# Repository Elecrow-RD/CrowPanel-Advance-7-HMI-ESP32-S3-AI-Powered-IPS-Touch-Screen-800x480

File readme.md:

## Menu
### 1, Product picture
### 2, Product version number
### 3, product information
### 4, Use the driver module
### 5,Quick Start
### 6,Folder structure.
### 7,Pin definition
### 8,Guidelines for downloading some of the files from the github repository

### 1, Product picture

#### 2, Product version number

|      | Hardware | Software | Remark |
| ---- | -------- | -------- | ------ |
| 1    | V1.0     | V1.0     | old    |
| 2    | V1.2     | V1.2     | old |
| 3    | V1.3     | V1.3     | old |
| 4    | V1.4     | V1.3     | old |
| 4    | V1.5     | V1.3     | latest |

### Version update points:

**Version 1.2**

① Version 1.2 updated the control of backlight on the basis of the original, the backlight of version 1.2 is controlled by STC8H1K28 microcontroller, and the backlight is lit in the program by sending the value to this microcontroller address (0x30).
The values are 0x05, 0x06, 0x07, 0x08, 0x09 and 0x10, where 0x05 switches off the backlight and 0x10 is the maximum brightness.

**To set a different brightness level, you must first send 0x10 to turn on the screen, and then send another value to adjust the brightness.**

The control of the buzzer is similar to that of the backlight: sending 0x15 activates the buzzer, while sending 0x16 deactivates it.

The speaker is controlled in the same manner: sending 0x17 activates the speaker, while sending 0x18 deactivates it.

② Version 1.2 has a new option for function switching, see above for details.
When using the case, please select the corresponding program to test or modify according to the version number of your motherboard.

**Version 1.3**

① Version 1.3 introduces an updated backlight control function. In this iteration, the backlight is managed by the STC8H1K28 microcontroller. The programme illuminates the backlight by transmitting numerical values to the microcontroller's address (0x30).
Brightness adjustment spans 0-245 levels, where 0 denotes maximum brightness, 244 represents minimum brightness, and 245 disables the backlight.

The buzzer control principle mirrors that of the backlight: sending 246 activates the buzzer, while sending 247 deactivates it.

**Version 1.4**

Only the button component has been updated. All other hardware and I/O pins remain the same as in the 1.3 version.

**Version 1.5**

Version 1.5 is simply an update to the previous version that modifies the packaging of the touchscreen FPC connector. There are no other differences.

### 3, product information

| Main Chip-ESP32-S3-WROOM-1-N16R8         |                                                              |
| -------------------------------------------- | ------------------------------------------------------------ |
| CPU/SoC                                      | high-performance Xtensa 32-bit LX7 dual-core processor, with up to 240MHz |
| System Memory                                | 512KB SRAM、8M PSRAM                                         |
| Memory                                       | 16M Flash，384KB ROM                                         |
| Development Language                         | MicroPython、C/C++                                           |
| Development Environment                      | ESP-IDF、Arduino IDE、PlatformIO、MicroPython         |
| **Screen**                                   |                                                              |
| Size                                         | 7.0 inch                                                     |
| Diver IC                                     | SC7277                                                       |
| Resolution                                   | 800*480                                                      |
| Display Panel                                | IPS Panel                                                    |
| Touch Panel                                  | Capacitive Single Touch                                      |
| Viewing Angle                                | 178°                                                         |
| Brightness                                   | 400 cd/m²(Typ.)                                              |
| Color Depth                                  | 16-bit                                                       |
| **Wireless Communication - Onboard Antenna** |                                                              |
| WiFi                                         | Support 2.4GHz, 802.11a/b/g/n                                |
| Bluetooth                                    | Support Bluetooth 5.0 and BLE                                |
| Other                                        | **Zigbee、LoRa、nRF2401、Matter、Thread and Wi-Fi 6 (Optional)** |
| **Interface/Function**                       |                                                              |
| Interface                                    | USB port, UART, I2C, SD card slot, battery socket, speaker port, microphone, etc. |
| Function                                     | RTC clock, audio amplifier, volume control, battery charge management, USB to UART, etc. |
| **Button/LED Indicator**                     |                                                              |
| Reset Button                                 | Yes, press to reset the device                               |
| Boot Button                                  | Yes, press and hold the power button to burn the program     |
| PWR                                          | Power indicator                                              |
| CHG                                          | Lithium battery charging status, completion indication       |
| **Other**                                    |                                                              |
| Installation method                          | Back hanging, fixed hole                                     |
| Operating temperature                        | -20~70 °C                                                    |
| Storage temperature                          | -30~80 °C                                                    |
| Power Input                                  | 5V/2A, USB or UART terminal                                  |
| Active Area                                  | 156mm*87mm                                                   |
| Dimensions                                   | 181.26\*108.36*16mm                                           |

### 4, Use the driver module

| Name | dependency library                      |
| ---- | --------------------------------------- |
| LVGL | lvgl/lvgl@8.3.3                         |
|      | Adafruit GFX Library<br/>version=1.11.0 |

### 5,Quick Start
### Arduino IDE starts

#### Teaching Case Path：./example/example_code7.0

1.Download the library files used by this product to the 'libraries' folder.

C:\Users\Documents\Arduino\libraries\

2.Open the Arduino IDE

3.Open the code configuration environment and burn it

### ESP-IDF starts

#### Teaching Case Path：./example/idf_code

1.Right-click on an empty space in the project folder and select "Open with VS Code" to open the project.

2.In the IDF plug-in, select the port, then compile and flash

### 6,Folder structure.

|--3D file： Contains 3D model files (.stp) for the hardware. These files can be used for visualization, enclosure design, or integration into CAD software.

|--Datasheet: Includes datasheets for components used in the project, providing detailed specifications, electrical characteristics, and pin configurations.

|--Eagle_SCH&PCB: Contains **Eagle CAD** schematic (`.sch`) and PCB layout (`.brd`) files. These are used for circuit design and PCB manufacturing.

|--example: Provides example code and projects to demonstrate how to use the hardware and libraries. These examples help users get started quickly.

|--factory_firmware: Stores pre-compiled factory firmware that can be directly flashed onto the device. This ensures the device runs the default functionality.

|--factory_sourcecode:  Contains the source code for the factory firmware, allowing users to modify and rebuild the firmware as needed.

|--libraries: Includes necessary libraries required for compiling and running the project. These libraries provide drivers and additional functionalities for the hardware.

|--Squareline_studio Instructions for use: Squareline_studio instructions: Demonstrate the use of squareline studio.

### 7,Pin definition

#define HSPI_MISO  4

#define HSPI_MOSI  6

#define HSPI_SCLK  5

#define HSPI_SS    19

#define SD_MOSI 6

#define SD_MISO 4

#define SD_SCK  5

#define SD_CS   7 //The chip selector pin is not connected to IO

#define I2S_DOUT 12

#define I2S_BCLK 13

#define I2S_LRC 11

cfg.pin_sclk = 42;  // SPI、SCLK

cfg.pin_mosi = 39;  // SPI、CLK

cfg.pin_miso = -1;  // SPI、MISO

cfg.pin_dc = 41; 

#define TOUCH_GT911_SCL 16

#define TOUCH_GT911_SDA 15

### 8,Guidelines for downloading some of the files from the github repository

##### 1, open the link in your browser: https://downgit.github.io/

##### 2, paste the URL of the GitHub destination folder in the input box (example format: `https://github.com/username/repository name/tree/branch name/folder path`)

##### 3, even a that way to download the file.

①Click the “Create Download Link” button to create a download link, copy the link and open it with your browser to download the contents of the corresponding folder directly.

②Click Download, and you can also download it directly.

#### Note: DownGit downloads are stored by default in **your browser's default downloads folder**, usually:

- **Windows**: `C:\Users\your username\Downloads\` (downloads folder)
- **macOS**: `~/Downloads/` (downloads folder)
- **Linux**: `~/Downloads/` (Downloads folder)

If you change the default download path in your browser, the file will be stored in the download location you set. You can find the downloaded file path in your browser's **Download History** (shortcut `Ctrl + J` or `Cmd + J`).

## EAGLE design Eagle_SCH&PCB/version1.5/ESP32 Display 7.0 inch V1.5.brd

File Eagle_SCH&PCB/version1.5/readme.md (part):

# 7.0-Inch Hardware Identity Product Hardware Driver Guide

| Item | Details |
|---|---|
| Document Version | V1.0 |
| Corresponding Hardware Documentation | `ESP32 Display 7.0 inch V1.5.sch/.brd`, `ESP32-Display-7.0-inch-V1.5.pdf` |
| Preparation Date | 2026-07-30 |
| Author | OpenAI Codex (cross-compiled from project materials) |
| Scope | The 7.0-inch CrowPanel Advance HMI hardware in this repository and the accompanying Arduino validation projects |

> **Priority of conclusions:** Board-level driver code that has been successfully tested or delivered with the project > EAGLE `.sch` net connections > PDF visual annotations > general-purpose chip datasheets. This document uses the pins and parameters actually used by the code as the porting baseline. Functions confirmed only by the schematic and lacking validation programs in the repository are explicitly marked “To Be Verified” and must not be treated as production software acceptance results.

## 1. Document Sources and Evidence Levels

### 1.1 Input Materials

1. `version1.5/ESP32 Display 7.0 inch V1.5.sch`: Primary source for components, net names, and electrical connections.
2. `version1.5/ESP32-Display-7.0-inch-V1.5.pdf`: Source for functional sections, DIP-switch instructions, and visual verification.
3. `Arduino/lesson-01` through `lesson-09`: Examples for serial communication, audio, LCD/LVGL, TF card, expansion ports, nRF24L01, SX1262/LoRaWAN, and UART/Zigbee.
4. `Arduino/SD_CrowPanel_ESP32_Advance_HMI_4_3_5_0_7_0`: An additional TF card display example, used only to identify differences in historical parameters.
5. Library versions included with the repository: Arduino-ESP32 3.3.8 (specified in the README), LovyanGFX 1.2.25, LVGL 9.1.0, ESP32-audioI2S 3.4.7, RF24 1.6.1, and RadioLib 7.7.1.

### 1.2 Evidence Levels

| Level | Meaning | Usage Rule |
|---|---|---|
| A: Code-verified | Complete initialization and application read/write operations exist in the project examples | May be used directly as the porting baseline, but regression testing in the target firmware is still required |
| B: Schematic-confirmed | Complete connections exist in the schematic, but the repository has no corresponding read/write example | Pin connections are reliable; protocol parameters require first-board validation |
| C: External-module example | The example targets a module connected to an expansion port and does not represent an onboard component | Applicable only when the corresponding peripheral is installed and the DIP switches are configured correctly |
| D: Inferred/To Be Confirmed | Conflicts exist in model, address, or production-batch information | Must be verified against the physical unit and chip datasheet before use |

## 2. Product Architecture and Peripheral Overview

The main controller is an ESP32-S3-WROOM-1 module. The MCU section title in the schematic PDF is labeled `ESP32-S3-N16R8`, indicating that the target configuration is likely 16 MB Flash + 8 MB PSRAM; however, the laser marking on the physical module and the Arduino build menu must take precedence. The board also includes an STC8H1K28 auxiliary control MCU, which handles backlight control, touch reset, buzzer control, amplifier/board-level power control, and other functions over a shared I²C bus.

| Category | Component/Interface | Primary Connections | Driver Method | Level |
|---|---|---|---|---|
| Main Controller | ESP32-S3-WROOM-1 (shown as N16R8) | All main-controller GPIOs; USB-UART | Arduino-ESP32 / ESP-IDF HAL | A/D |
| Board Control MCU | STC8H1K28-36I-LQFP32 | I²C GPIO15/16, address `0x30`; GPIO1 recovery path | I²C single-byte commands | A |
| Display | 7.0-inch 800×480 RGB IPS | GPIO3/7/9~14/17/18/21/38/45~48, 39~42 | 16-bit RGB parallel interface + DMA | A |
| Touch | GT911 capacitive touch | SDA15, SCL16; INT to GPIO1; RST controlled by board control MCU | I²C at 400 kHz, address `0x5D` | A |
| Backlight | MT9201 boost constant-current driver + board control MCU | LCD LEDA/LEDK; MCU controls EN/power | I²C commands 0~245 | A |
| TF Card | MicroSD card slot | GPIO4 MISO, 5 SCK, 6 MOSI; CS fixed in hardware | SPI/FS/SD, 40 MHz | A |
| Audio Output | NS4168 digital-input amplifier + speaker connector | GPIO4 SDATA, 5 BCLK, 6 LRCLK | I²S; board control command `248` enables output | A |
| Digital Microphone | LMD3526B261 PDM MIC | GPIO19 CLK, GPIO20 DATA, through CH486F | PDM/I²S RX | B |
| RTC | PCF8563-compatible component + 32.768 kHz + CR1220 | SDA15, SCL16 | I²C, typically address `0x51` | B/D |
| Buzzer | 5025 passive buzzer + NPN | Controlled by STC8H1K28 P2.7 | Auxiliary MCU PWM/GPIO | B |
| Wireless Expansion | J9/J12 expansion ports | SPI GPIO4/5/6; control GPIO19/20, plus GPIO2/8 | SPI + GPIO/IRQ | C |
| nRF24L01 | External 2.4 GHz module | MISO4/MOSI6/SCK5, CSN19, CE20 | RF24; 250 kbps, CH50 | C |
| SX1262 | External LoRa module | NSS8, DIO1 20, RST19, BUSY2, SPI4/5/6 | RadioLib / LoRaWAN | C |
| UART Expansion | J2/J14/multiplexed port | UART0; or GPIO19 RX, GPIO20 TX | UART 8N1, example uses 115200 | A/C |
| I²C Expansion | J13/J11 | SDA15, SCL16, 3.3 V/GND | I²C, shared onboard bus | A/C |
| GPIO Expansion | J11 | GPIO2, GPIO8, I²C, power | 3.3 V GPIO | B/C |
| USB/Programming | USB-C + CH340K + automatic programming circuit | ESP UART0, EN, GPIO0 | USB-UART / automatic reset and programming | A |
| Battery/Charging | TP4059 + battery connector | USB/5 V, VBAT, CHRG/DONE to board control MCU | Hardware charging, MCU status acquisition | B |
| Main Power | RY3420/HM3416H DC-DC, etc. | VIN → 3.3 V; separate boost supply for display backlight | Hardware power management | B |
| Wi-Fi/BLE | ESP32-S3 integrated radio | Module antenna | Arduino WiFi/BLE stack | A (Wi-Fi) |
| Indicators/Buttons | BOOT, RESET, power/charging LEDs | GPIO0, EN; board control MCU | Active-low buttons/hardware indicators | A/B |

## 3. ESP32-S3 GPIO Baseline Table

| GPIO | Actual Function in Code | Schematic Net/Connection | Multiplexing and Considerations |
|---:|---|---|---|
| 0 | CS parameter passed to the SD library by the TF example; BOOT | `IO0_BOOT`, active-low BOOT button | **Boot strapping pin**; MicroSD CS is not physically connected to GPIO0 and must not be assumed to be controllable as a chip-select signal |
| 1 | Touch/board-control fault recovery: low pulse for 120 ms, then configured as input | `IO1_TP_INT`, touch FPC INT | No touch interrupt is registered at runtime; must not be continuously driven in push-pull mode |
| 2 | SX1262 BUSY; GPIO expansion | J11 GPIO; schematic `IO2` | Used as an input with external LoRa; consider boot state and peripheral signal levels |
| 3 | LCD R3 (logical R3 in code, physical panel R6) | `IO3_R6` | Dedicated to LCD; do not reuse |
| 4 | SD MISO / I²S SDATA / external SPI MISO | Through CH486F analog switch | Mutually exclusive; selected by DIP switch |
| 5 | SD SCK / I²S BCLK / external SPI SCK | Through CH486F analog switch | Mutually exclusive; clock lines must not be connected to multiple channels simultaneously |
| 6 | SD MOSI / I²S LRCLK / external SPI MOSI | Through CH486F analog switch | Mutually exclusive |
| 7 | LCD R0 (panel R3) | `IO7_R3` | Dedicated to LCD |
| 8 | SX1262 NSS; GPIO expansion | J11 GPIO; schematic `IO8` | Used as chip select in the LoRa example |
| 9~14 | LCD G0~G5 (panel G2~G7) | RGB data | Dedicated to LCD |
| 15 | I²C SDA | RTC, GT911, STC, I²C port | External open-drain, pulled up to 3.3 V; shared bus |
| 16 | I²C SCL | RTC, GT911, STC, I²C port | External open-drain, pulled up to 3.3 V; shared bus |
| 17,18 | LCD R1,R2 | RGB data | Dedicated to LCD |
| 19 | Expansion IRQ/CSN/RST/UART RX or PDM CLK | Through CH486F to wireless port/microphone | Multiplexed as a pair with GPIO20; enable only after configuring the DIP switches |
| 20 | Expansion CE/DIO1/UART TX or PDM DATA | Through CH486F to wireless port/microphone | Multiplexed as a pair with GPIO19 |
| 21 | LCD B0 | RGB data | Dedicated to LCD |
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
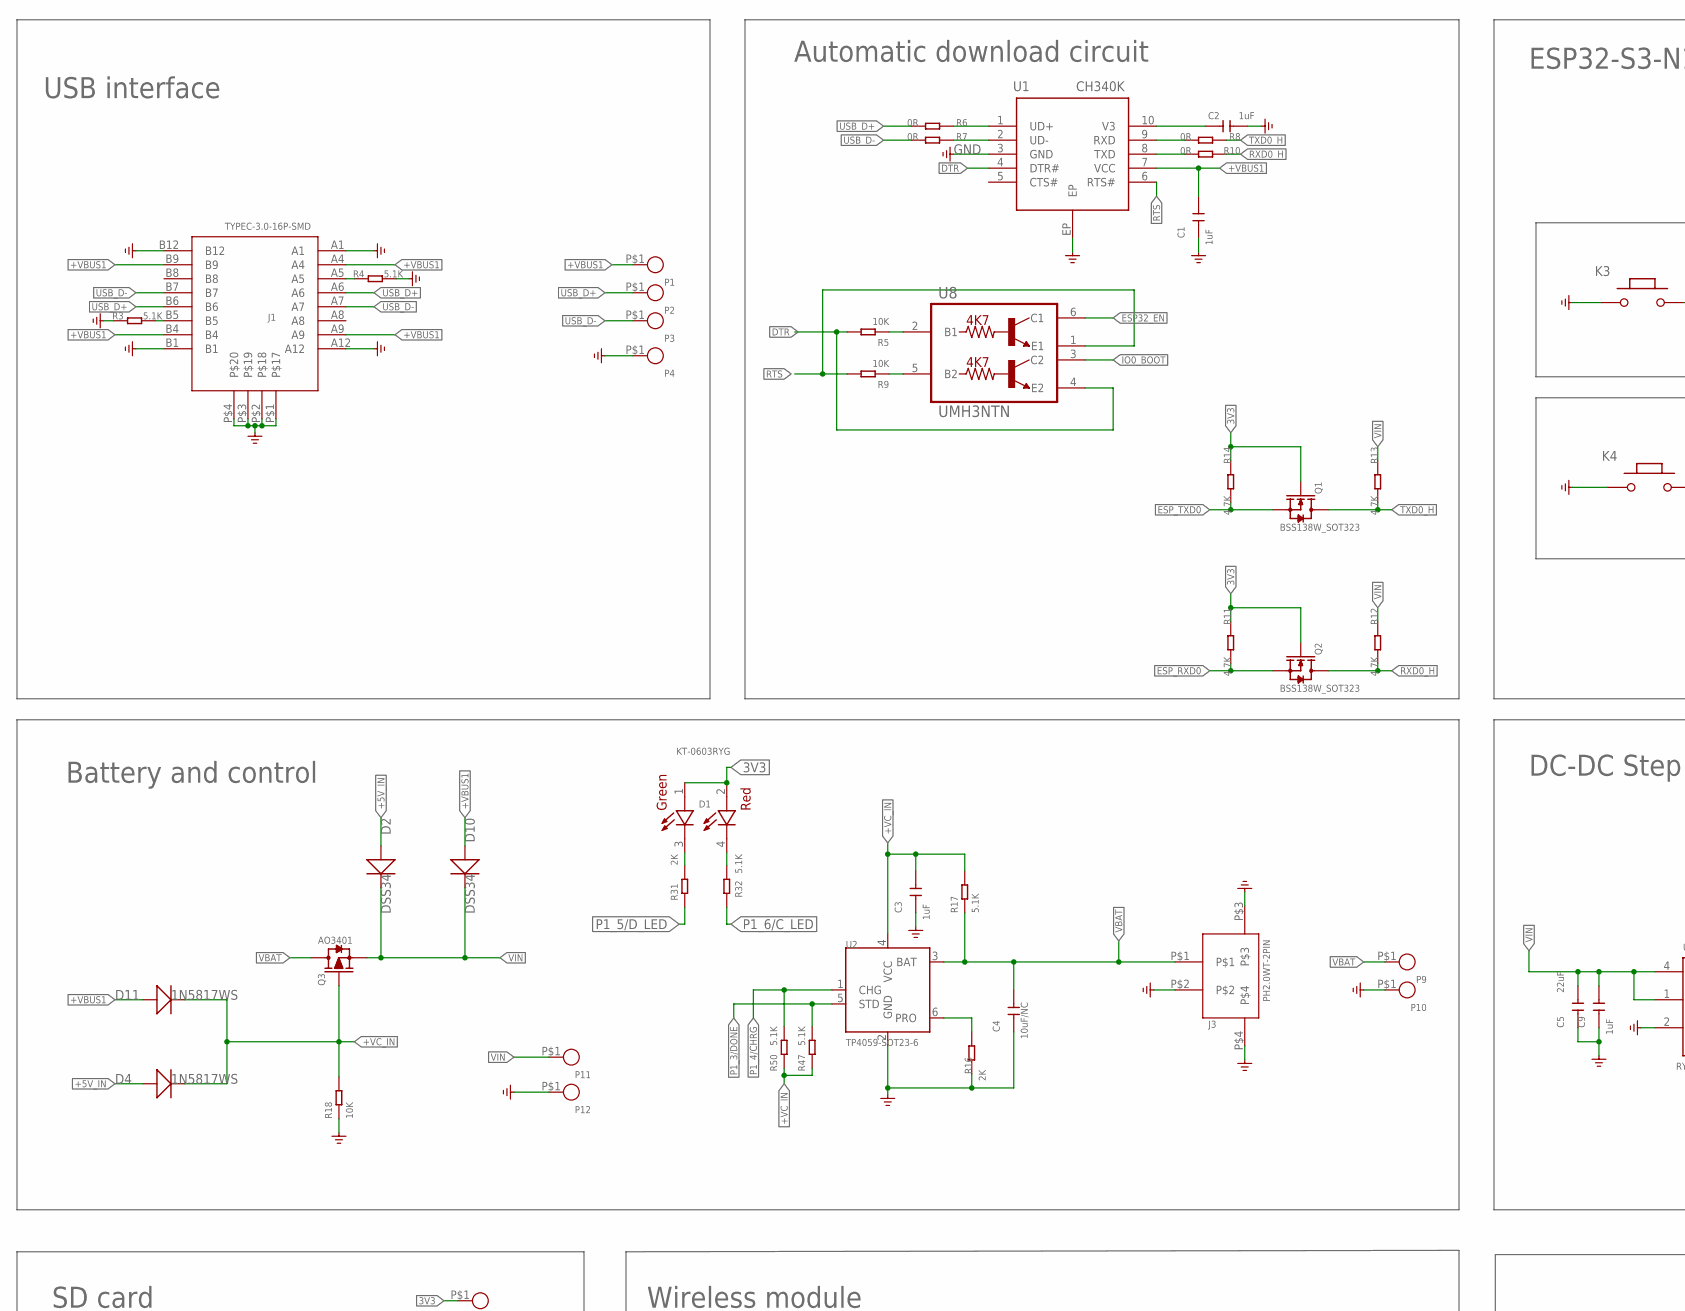
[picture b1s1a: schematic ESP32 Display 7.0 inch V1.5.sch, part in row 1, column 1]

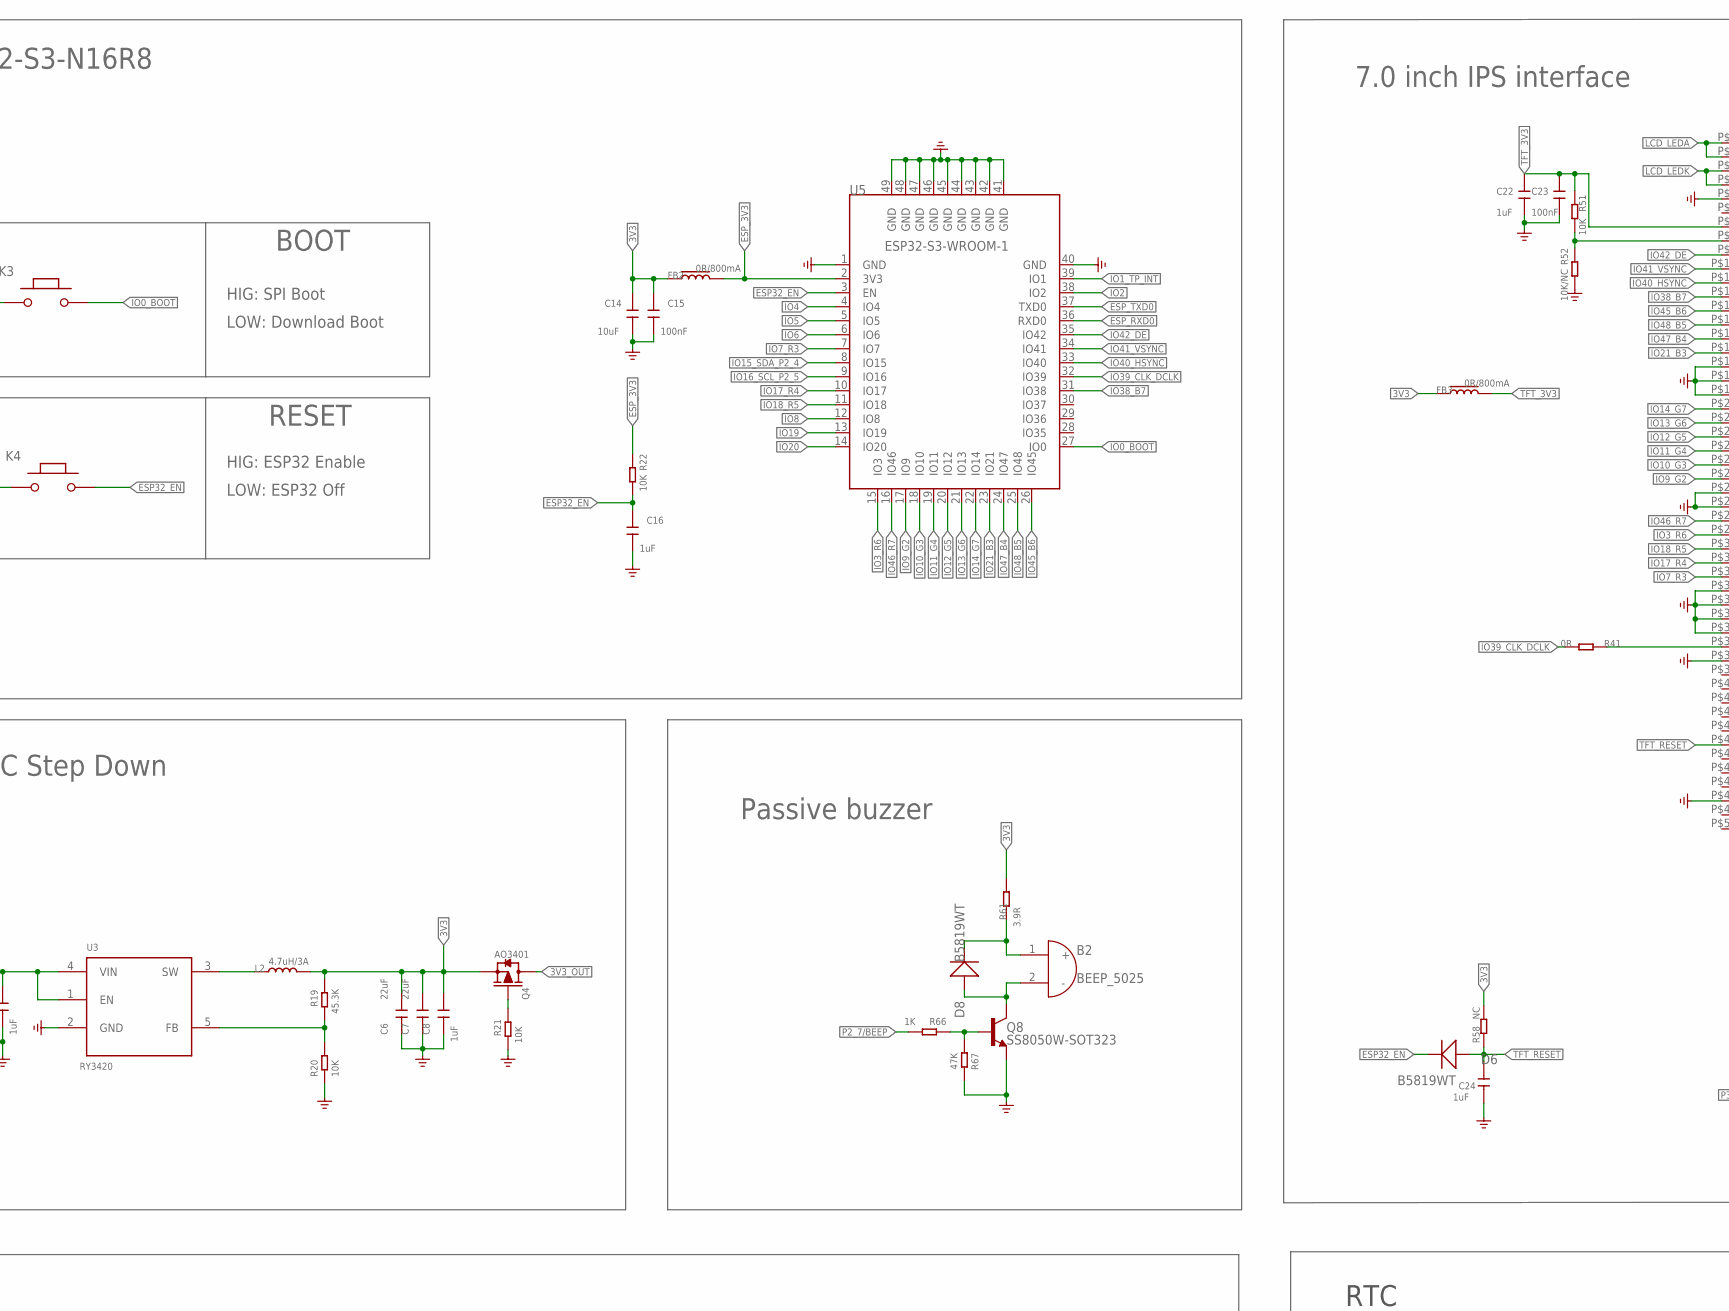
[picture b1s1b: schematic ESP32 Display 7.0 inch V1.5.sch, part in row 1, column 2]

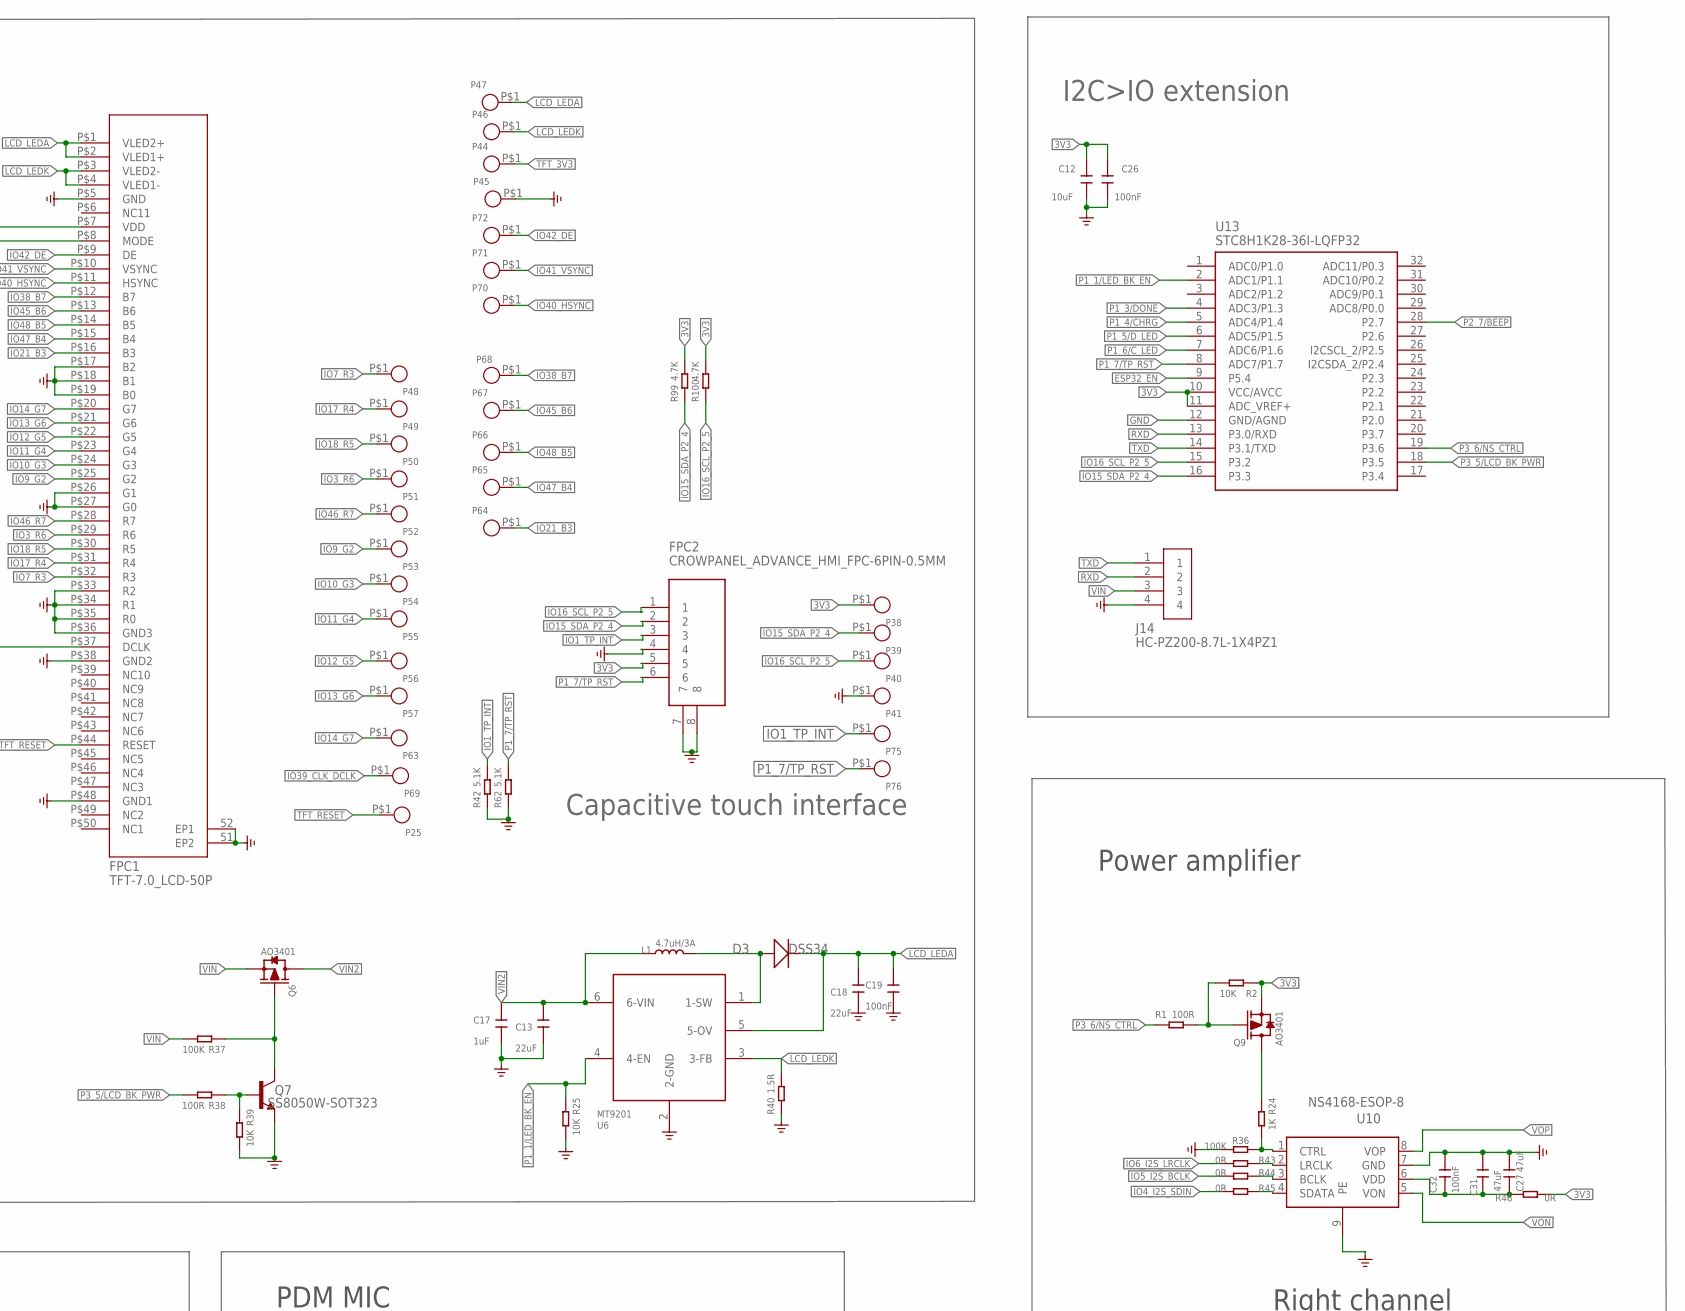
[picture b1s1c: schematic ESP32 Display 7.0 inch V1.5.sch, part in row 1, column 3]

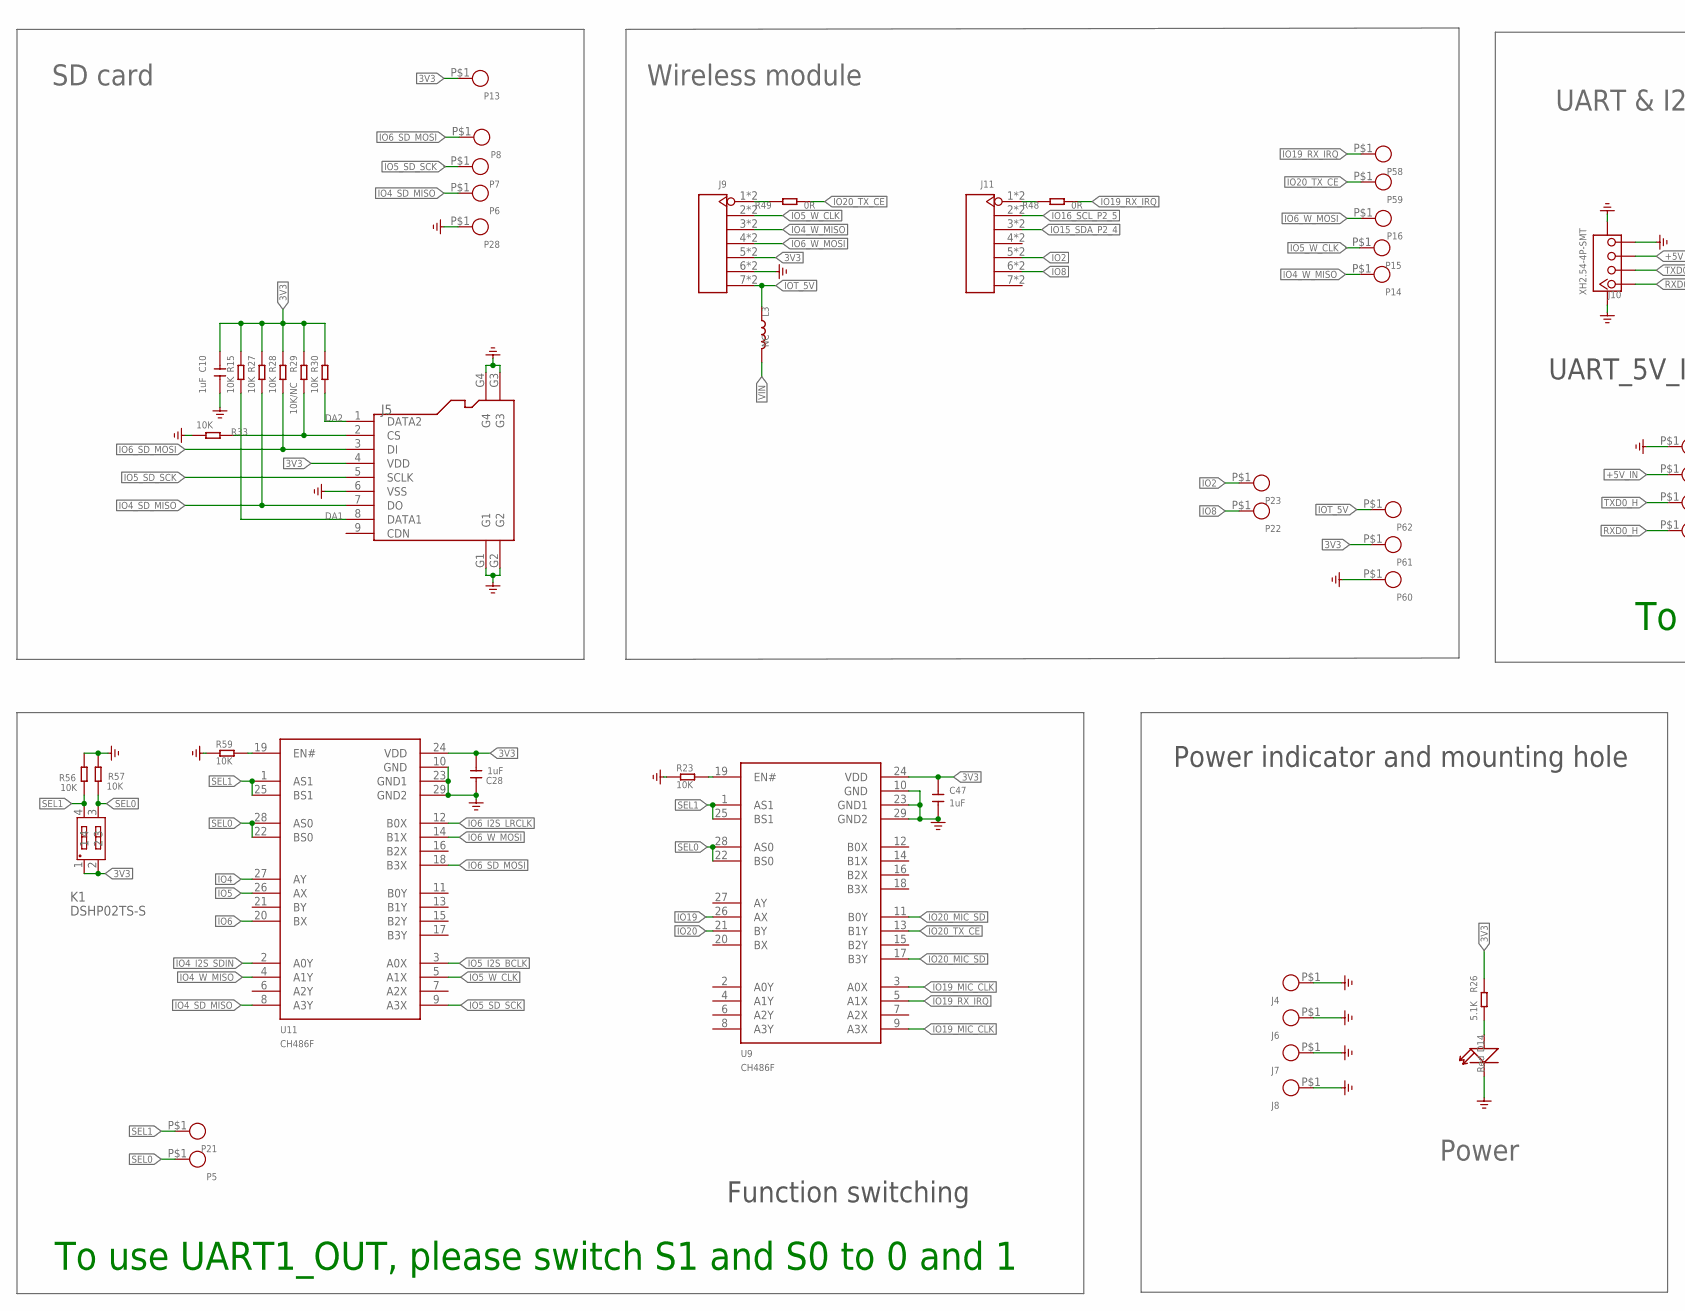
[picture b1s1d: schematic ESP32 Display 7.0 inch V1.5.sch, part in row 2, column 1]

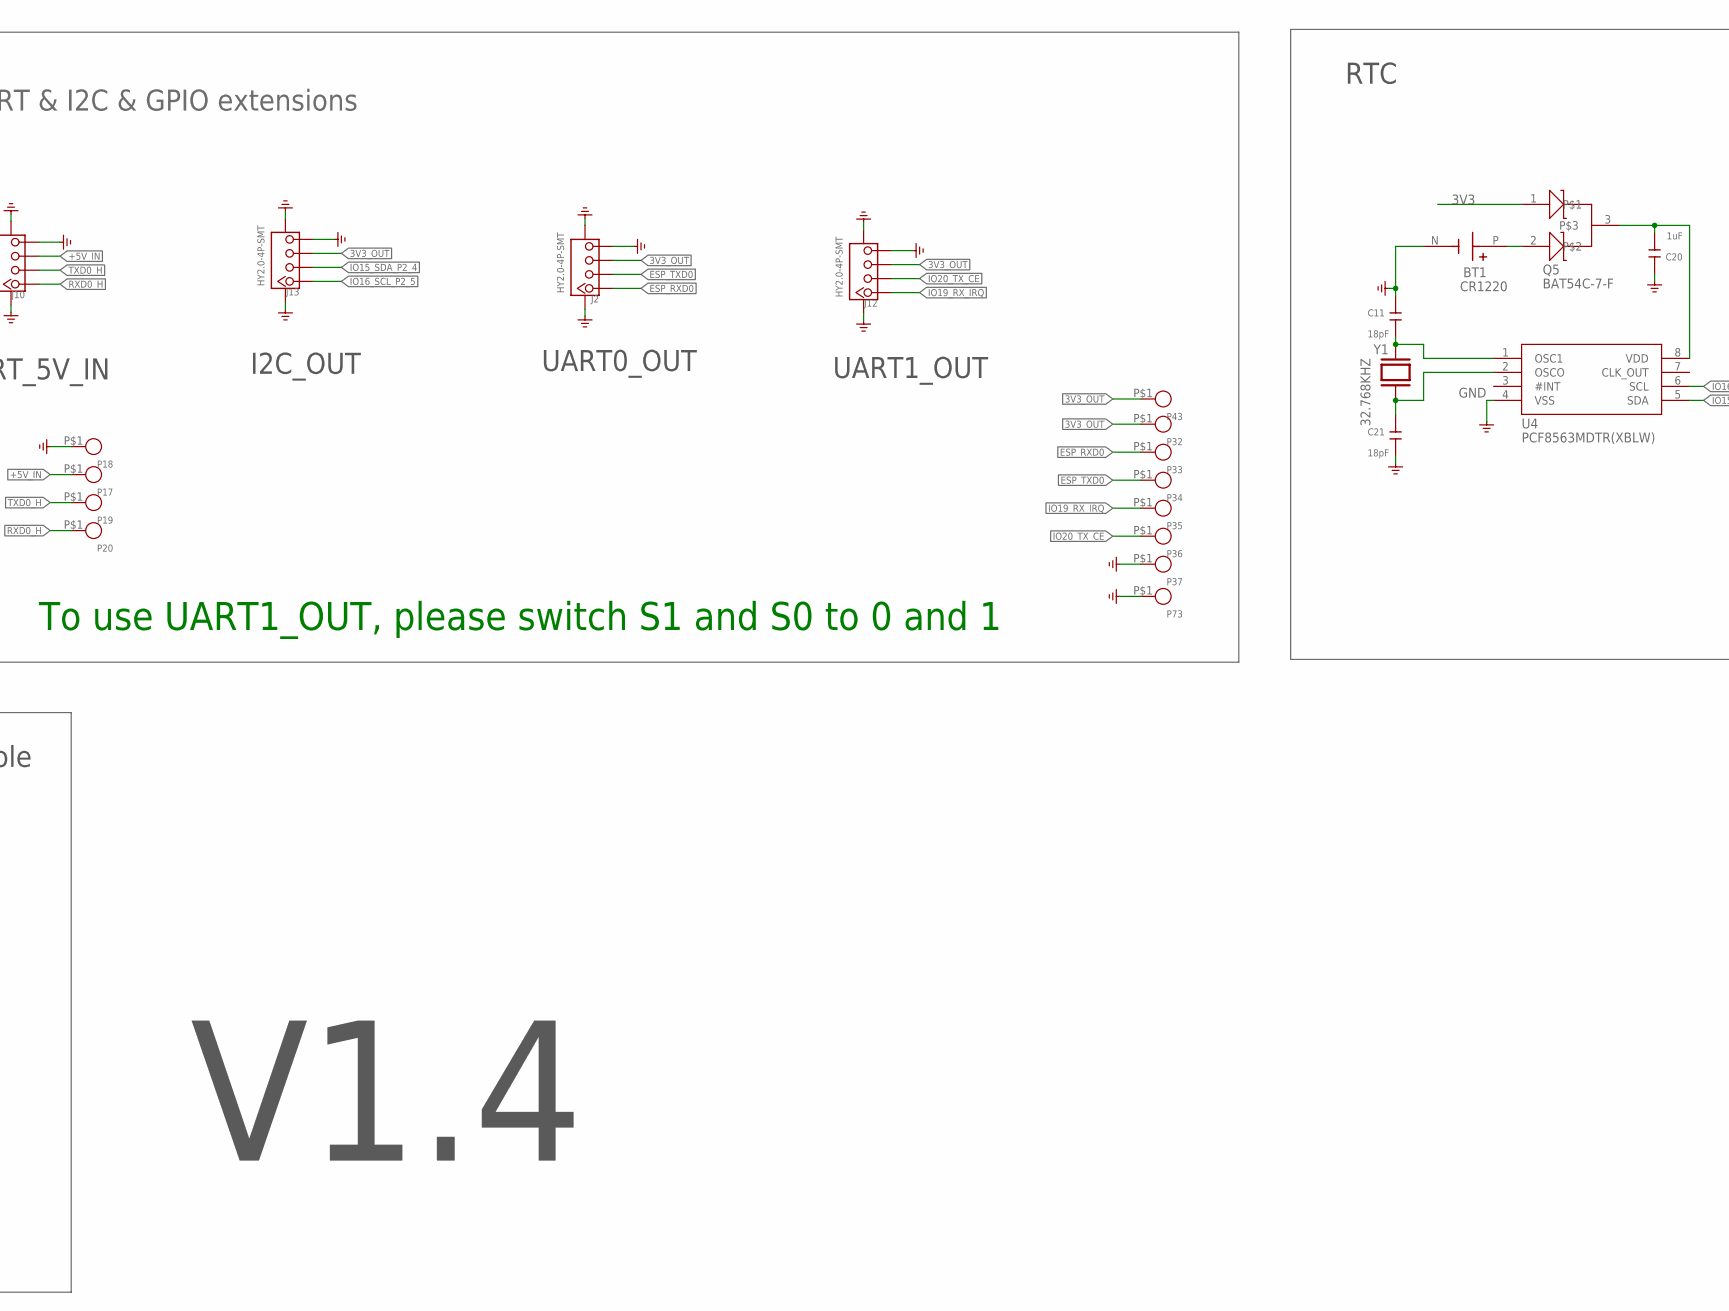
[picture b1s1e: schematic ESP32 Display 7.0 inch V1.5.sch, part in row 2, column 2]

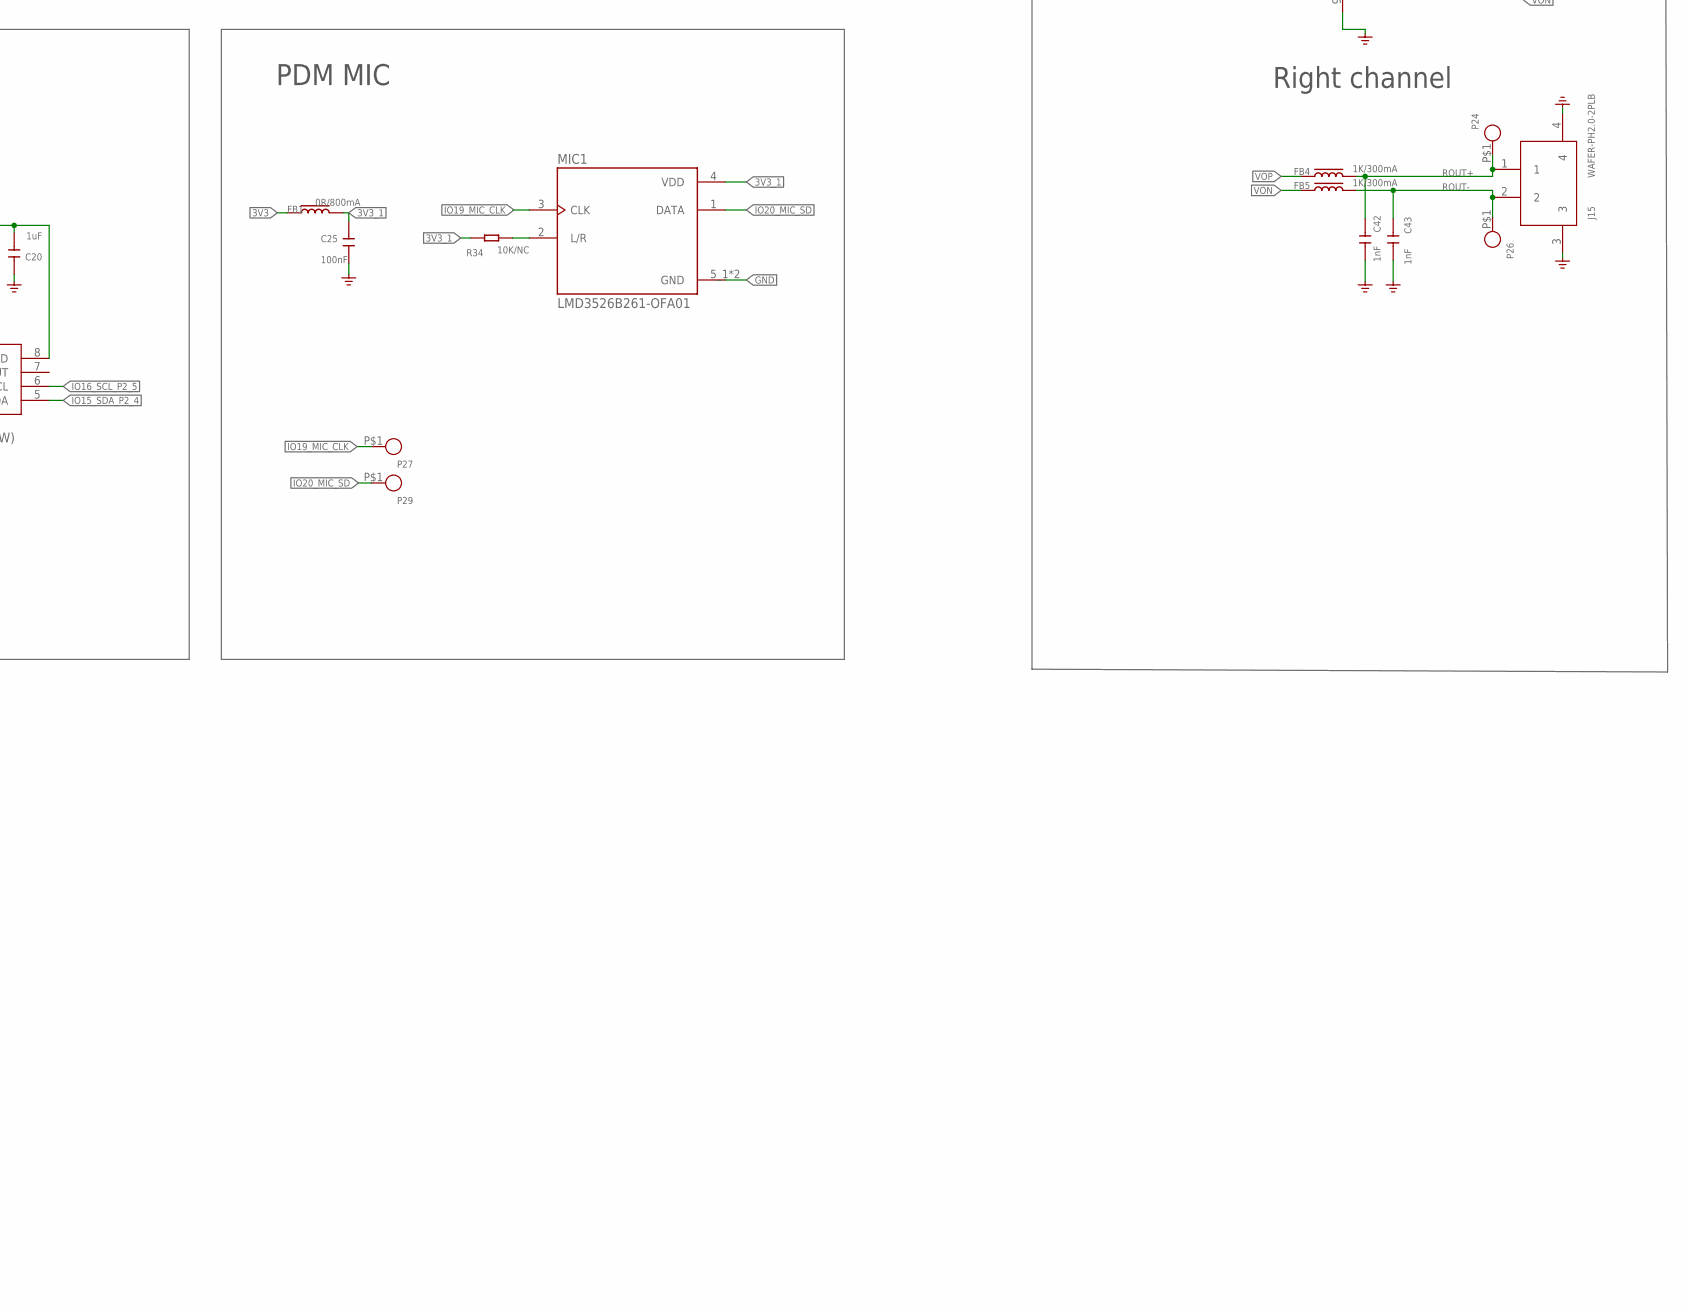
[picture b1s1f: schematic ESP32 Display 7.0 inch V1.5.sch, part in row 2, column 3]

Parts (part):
B2: BEEP_5025
BT1: CR1220
C1, C2, C3, C8, C9, C10, C16, C17, C20, C22, C24, C28, C47: 1uF; C0603
C4: 10uF/NC; C0603
C5, C6, C7, C13, C18: 22uF; C0805
C11, C21: 18pF; C0603
C12, C14: 10uF; C0603
C15, C19, C23, C25, C26, C32: 100nF; C0603
C27, C31: 47uF; C0805
C42, C43: 1nF; C0603
D1: KT-0603RYG; LED_KT-0603RYG
D2, D3, D10: DSS34; D_SOD123FL
D4, D11: 1N5817WS; D_SOD323
D6, D8: B5819WT; D_SOD523
D14: Red; LED0603
FB1, FB2, FB3: 0R/800mA; L0603
FB4, FB5: 1K/300mA; L0603
FPC1: TFT-7.0_LCD-50P; FPC-P0.5MM-50P-SMD
FPC2: CROWPANEL_ADVANCE_HMI_FPC-6PIN-0.5MM
J1: TYPEC-3.0-16P-SMD; USB-3.0TYPEC-SMD
J2, J12, J13: HY2.0-4P-SMT; CONNECTOR_4P-SMD-2.0
J3: PH2.0WT-2PIN
J4, J6, J7, J8: THO-M3.25MM-HOLE; THO-M3.2*5MM-HOLE
J5: HOLDER-MICROSD-9P; 9P-SMD-W/-RING
J9, J11: HEADER-7P-18.28X2.5; H7-2.54-18.28X2.5X5MM
J10: XH2.54-4P-SMT; XH2.54-4P-SMD
J14: HC-PZ200-8.7L-1X4PZ1; TEST-PIN-4-2.0MM
J15: WAFER-PH2.0-2PLB; CONN-TH_2P-P2.00_XUNPU_WAFER-PH2.0-2PLB
K1: DSHP02TS-S; SW-SMD_DSHP02TS-S_1
K3, K4: PB157; 157SW
L1, L2: 4.7uH/3A; L0420
L3: NC; L0603
MIC1: LMD3526B261-OFA01; MIC-SMD_5P-L3.5-W2.7-P1.67
P1, P2, P3, P4, P5, P6, P7, P8, P9, P10, P11, P12, P13, P14, P15, P16, P17, P18, P19, P20, P21, P22, P23, P24, P25, P26, P27, P28, P29, P32, P33, P34, P35, P36, P37, P38, P39, P40, P41, P43, P44, P45, P46, P47, P48, P49, P50, P51, P52, P53, P54, P55, P56, P57, P58, P59, P60, P61, P62, P63, P64, P65, P66, P67, P68, P69, P70, P71, P72, P73, P75, P76: TEST_PADPAD-1.5MM; TEST_PAD-1.5MM
Q1, Q2: BSS138W_SOT323; MOS_SOT323
Q3, Q4, Q6, Q9: AO3401; PMOS_SOT23
Q5: BAT54C-7-F; SOT-23
Q7, Q8: SS8050W-SOT323; MOS_SOT323
R1, R38: 100R; R0603-SP
R2, R5, R9, R15, R18, R20, R21, R22, R23, R25, R27, R28, R30, R33, R39, R51, R56, R57, R59: 10K; R0603-SP
R3, R4, R17, R26, R32, R42, R47, R50, R62: 5.1K; R0603-SP
R6, R7, R8, R10, R41, R43, R44, R45, R46, R48, R49: 0R; R0603-SP
R11, R12, R13, R14, R99, R100: 4.7K; R0603-SP
R16, R31: 2K; R0603-SP
R19: 45.3K; R0603-SP
R24, R66: 1K; R0603-SP
R29, R34, R52: 10K/NC; R0603-SP
R36, R37: 100K; R0603-SP
R40: 1.5R; R0603-SP
R58: NC; R0603-SP
R61: 3.9R; R0603-SP
R67: 47K; R0603-SP
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
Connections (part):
3V3: C6.2, C7.2, C8.2, C10.2, C12.2, C14.2, C15.2, C26.2, C28.2, C47.1, D1.1, D1.2, FB1.1, FB2.1, FB3.1, FPC2.5, J5.4 (VDD), J9.5, J9.5-5 (5), K1.1, K1.2, L2.2, P13.P$1, P38.P$1, P61.P$1, Q1.1 (G), Q2.1 (G), Q4.2 (S), Q5.1, Q9.2 (S), R2.1, R11.1, R14.1, R15.2, R19.2, R26.2, R27.2, R28.2, R29.2, R30.2, R46.2, R58.2, R61.2, R99.2, R100.2, U9.24 (VDD), U11.24 (VDD), U13.10 (VCC/AVCC), U13.11 (ADC_VREF+)
3V3$: C2.2, U1.10 (V3)
3V3_1: C25.2, FB1.2, MIC1.4 (VDD), R34.2
3V3_OUT: J2.3, J12.3, J13.3, P32.P$1, P43.P$1, Q4.3 (D)
+5V_IN: D2.+, D4.+, J10.3, P17.P$1
+VBUS1: C1.2, D10.+, D11.+, J1.A4, J1.A9, J1.B4, J1.B9, P1.P$1, U1.7 (VCC)
+VC_IN: C3.2, D4.-, D11.-, Q3.1 (G), R17.2, R18.2, R47.2, R50.2, U2.4 (VCC)
DA1: J5.8 (DATA1), R15.1
DA2: J5.1 (DATA2), R30.1
DTR: R5.2, U1.4 (DTR#), U8.4 (E2)
ESP32_EN: C16.2, D6.-, K4.2, R22.2, U5.3 (EN), U8.6 (C1), U13.9 (P5.4)
ESP_3V3: FB2.2, R22.1, U5.2 (3V3)
ESP_RXD0: J2.1, P33.P$1, Q2.2 (S), R11.2, U5.36 (RXD0)
ESP_TXD0: J2.2, P34.P$1, Q1.2 (S), R14.2, U5.37 (TXD0)
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
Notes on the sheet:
BOOT
RESET
HIG: SPI Boot
LOW: Download Boot
HIG: ESP32 Enable
LOW: ESP32 Off
Power
USB interface
Automatic download circuit
Battery and control
RTC
ESP32-S3-N16R8
7.0 inch IPS interface
Capacitive touch interface
DC-DC Step Down
SD card
Wireless module
UART & I2C & GPIO extensions
Power indicator and mounting hole
I2C>IO extension
PDM MIC
Power amplifier
Right channel
Passive buzzer
Function switching
UART_5V_IN
I2C_OUT
UART0_OUT
UART1_OUT
To use UART1_OUT, please switch S1 and S0 to 0 and 1
V1.4

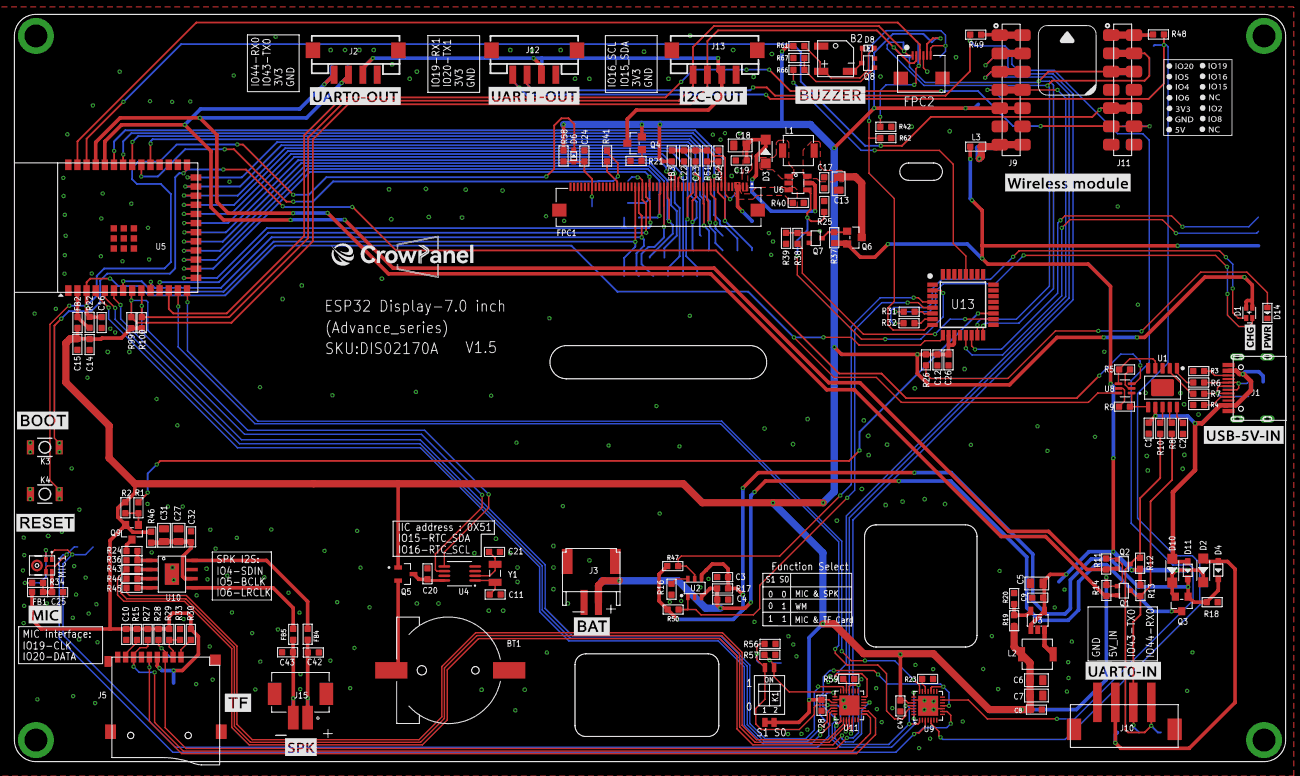
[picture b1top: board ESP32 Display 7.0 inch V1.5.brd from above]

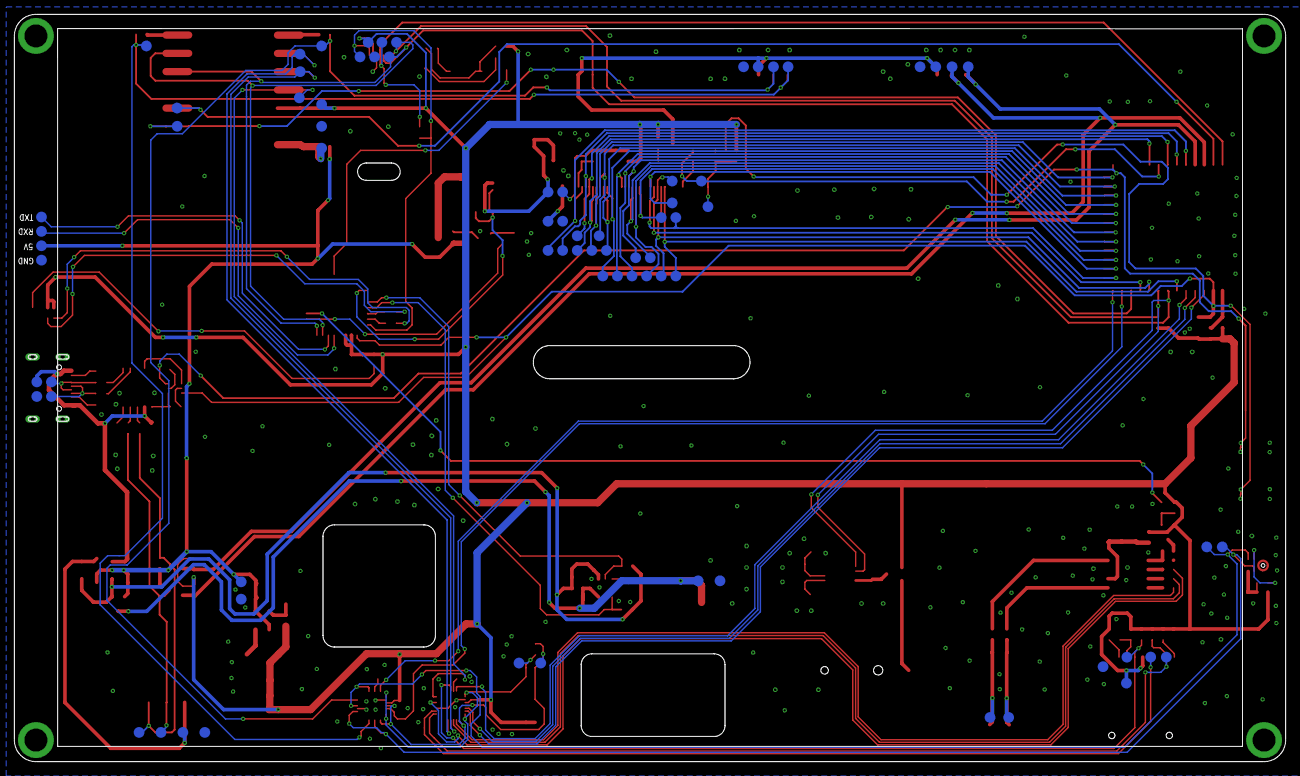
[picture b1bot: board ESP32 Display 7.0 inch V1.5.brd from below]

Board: 2 copper layers, 176.9 x 104.0 mm, 227 parts (73 on the bottom side), 129 nets.

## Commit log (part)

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2026-03-10 Update case study code links in readme
2026-03-10 Update readme for clarity and formatting
2026-04-17 Update readme with backlight brightness instructions
    Added instructions for adjusting backlight brightness levels.
2026-04-22 sync example/V1.3_V1.4
2026-05-10 sync example/V1.2
2026-05-29 Add V1.5 files
2026-06-02 sync example/V1.2/ESP-IDF
2026-06-02 Remove obsolete files
2026-06-03 libraries
2026-06-10 esp32
2026-06-24 Thread
2026-06-25 update .gitignore rules
2026-06-26 new code
